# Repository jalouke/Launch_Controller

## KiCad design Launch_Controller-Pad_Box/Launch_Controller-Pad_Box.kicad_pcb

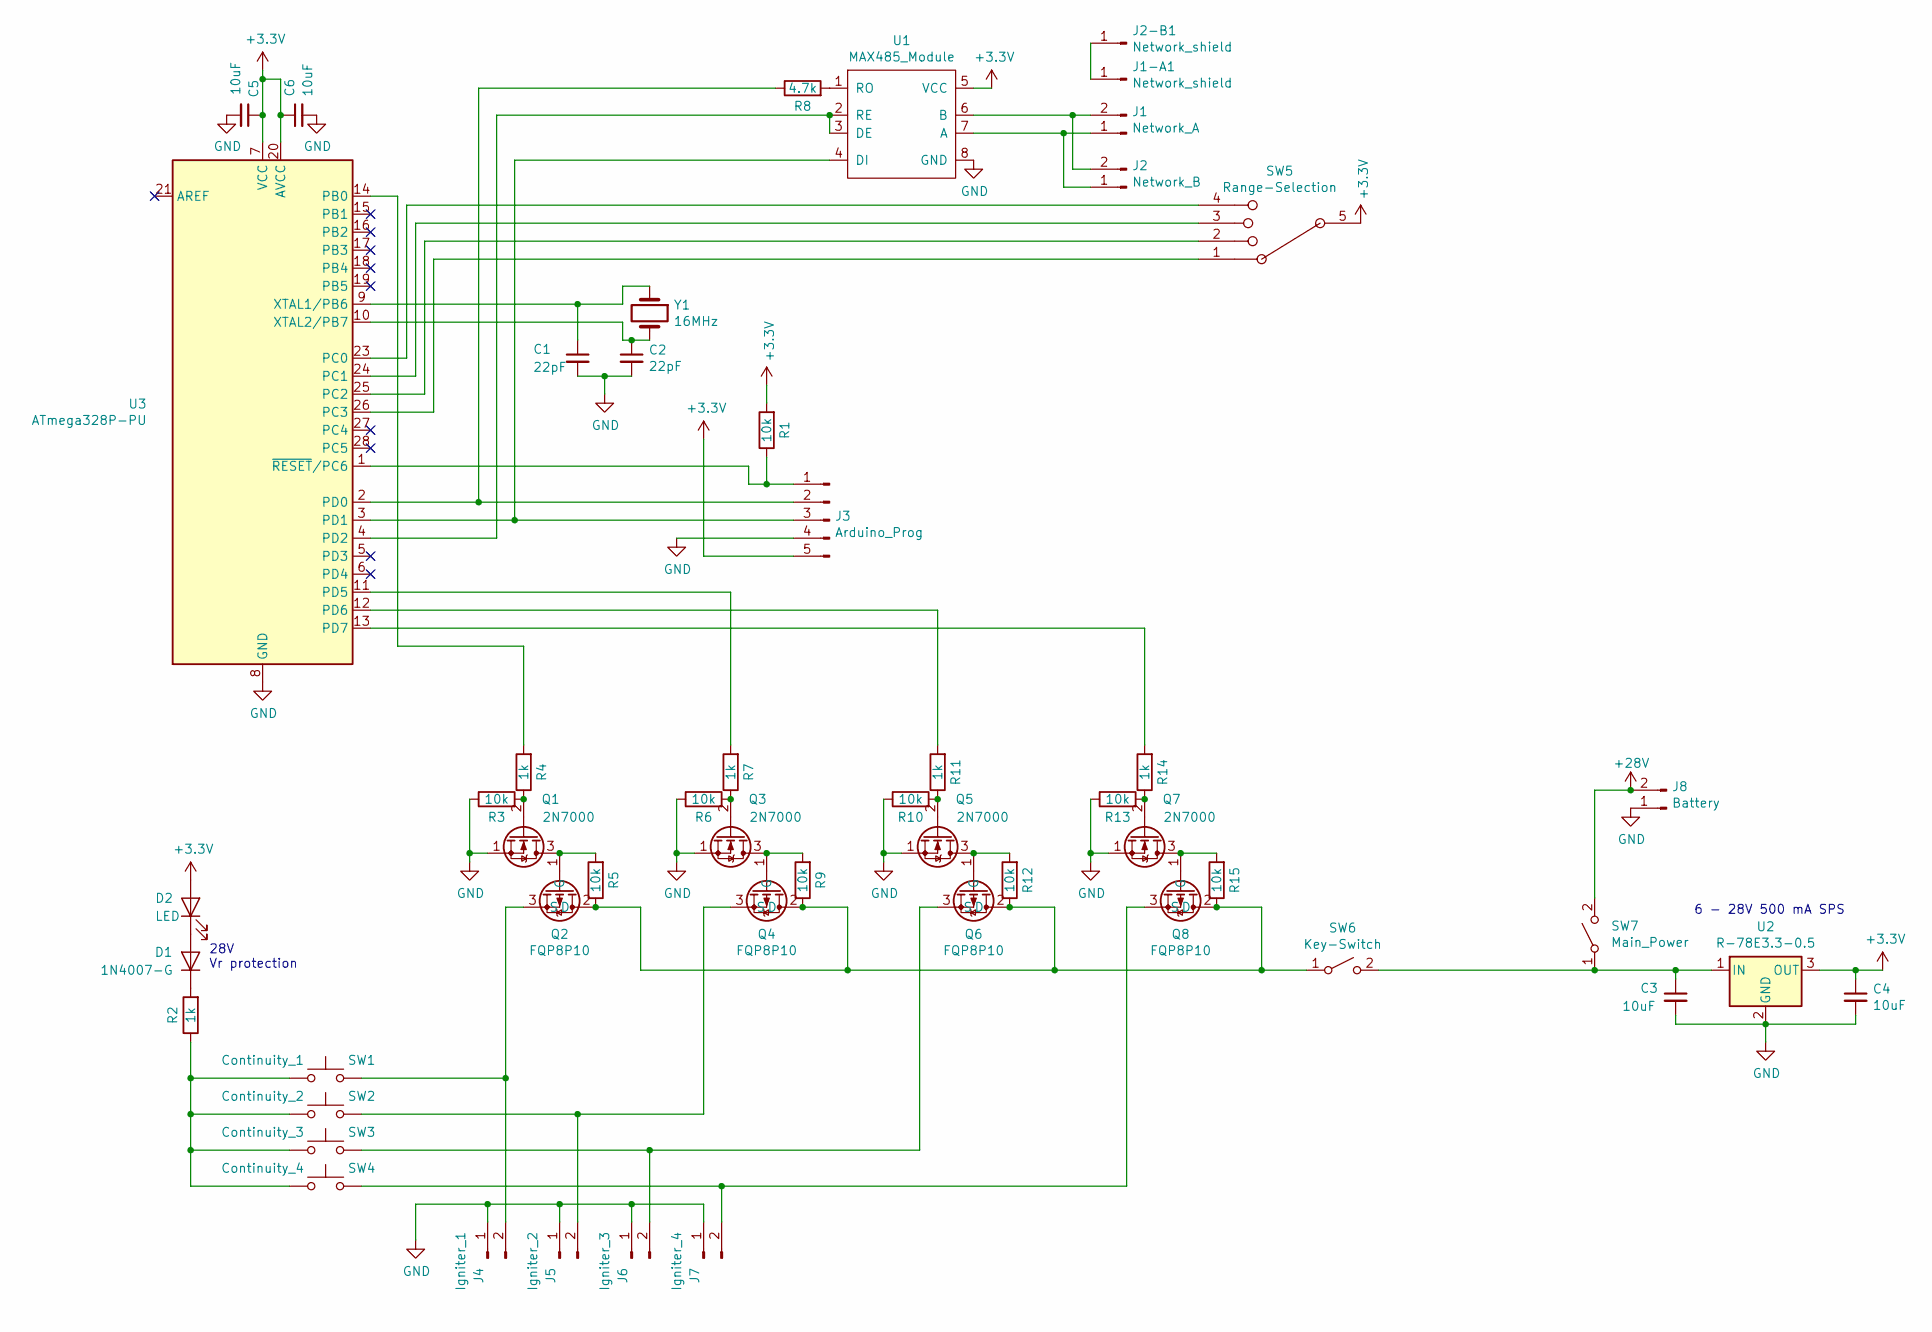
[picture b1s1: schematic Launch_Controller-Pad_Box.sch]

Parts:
C1, C2: 22pF; C_Disc_D3.0mm_W1.6mm_P2.50mm
C3, C4, C5, C6: 10uF; CP_Radial_D5.0mm_P2.00mm
D1: 1N4007-G; D_DO-41_SOD81_P10.16mm_Horizontal
D2: LED; PinHeader_2x01_P2.54mm_Vertical
J1: Network_A; PinHeader_1x02_P2.54mm_Vertical
J1-A1, J2-B1: Network_shield; PinHeader_1x01_P2.54mm_Vertical
J2: Network_B; PinHeader_1x02_P2.54mm_Vertical
J3: Arduino_Prog; PinHeader_1x05_P2.54mm_Vertical
J4: Igniter_1; PinHeader_1x02_P2.54mm_Vertical
J5: Igniter_2; PinHeader_1x02_P2.54mm_Vertical
J6: Igniter_3; PinHeader_1x02_P2.54mm_Vertical
J7: Igniter_4; PinHeader_1x02_P2.54mm_Vertical
J8: Battery; PinSocket_1x02_P2.54mm_Vertical
Q1, Q3, Q5, Q7: 2N7000; TO-92_Inline
Q2, Q4, Q6, Q8: FQP8P10; TO-220-3_Vertical
R1, R3, R5, R6, R9, R10, R12, R13, R15: 10k; R_Axial_DIN0207_L6.3mm_D2.5mm_P2.54mm_Vertical
R2, R4, R7, R11, R14: 1k; R_Axial_DIN0207_L6.3mm_D2.5mm_P2.54mm_Vertical
R8: 4.7k; R_Axial_DIN0207_L6.3mm_D2.5mm_P2.54mm_Vertical
SW1: Continuity_1; PinHeader_2x01_P2.54mm_Vertical
SW2: Continuity_2; PinHeader_2x01_P2.54mm_Vertical
SW3: Continuity_3; PinHeader_2x01_P2.54mm_Vertical
SW4: Continuity_4; PinHeader_2x01_P2.54mm_Vertical
SW5: Range-Selection; PinHeader_1x05_P2.54mm_Vertical
SW6: Key-Switch; PinHeader_1x02_P2.54mm_Vertical
SW7: Main_Power; PinHeader_1x02_P2.54mm_Vertical
U1: MAX485_Module; MAX485 Breakout
U2: R-78E3.3-0.5; Converter_DCDC_RECOM_R-78E-0.5_THT
U3: ATmega328P-PU; DIP-28_W7.62mm
Y1: 16MHz; Crystal_HC49-U_Vertical

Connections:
+3V3: C4.1, C5.1, C6.1, D2.2 (A), J3.5, R1.2, SW5.5, U1.5 (VCC), U2.3 (OUT), U3.7 (VCC), U3.20 (AVCC)
+28V: J8.2, SW7.2 (B)
GND: C1.2, C2.2, C3.2, C4.2, C5.2, C6.2, J3.4, J4.1, J5.1, J6.1, J7.1, J8.1, Q1.1 (S), Q3.1 (S), Q5.1 (S), Q7.1 (S), R3.1, R6.1, R10.1, R13.1, U1.8 (GND), U2.2 (GND), U3.8 (GND), U3.22 (GND)
unnamed: C1.1, U3.9 (XTAL1/PB6), Y1.1
unnamed: C2.1, U3.10 (XTAL2/PB7), Y1.2
unnamed: C3.1, SW6.2 (B), SW7.1 (A), U2.1 (IN)
unnamed: D1.1 (K), R2.2
unnamed: D1.2 (A), D2.1 (K)
unnamed: J1-A1.1, J2-B1.1
unnamed: J1.1, J2.1, U1.7 (A)
unnamed: J1.2, J2.2, U1.6 (B)
unnamed: J3.1, R1.1, U3.1 (~RESET~/PC6)
unnamed: J3.2, R8.1, U3.2 (PD0)
unnamed: J3.3, U1.4 (DI), U3.3 (PD1)
unnamed: J4.2, Q2.3 (S), SW1.2
unnamed: J5.2, Q4.3 (S), SW2.2
unnamed: J6.2, Q6.3 (S), SW3.2
unnamed: J7.2, Q8.3 (S), SW4.2
unnamed: Q1.2 (G), R3.2, R4.1
unnamed: Q1.3 (D), Q2.1 (G), R5.2
unnamed: Q2.2 (D), Q4.2 (D), Q6.2 (D), Q8.2 (D), R5.1, R9.1, R12.1, R15.1, SW6.1 (A)
unnamed: Q3.2 (G), R6.2, R7.1
unnamed: Q3.3 (D), Q4.1 (G), R9.2
unnamed: Q5.2 (G), R10.2, R11.1
unnamed: Q5.3 (D), Q6.1 (G), R12.2
unnamed: Q7.2 (G), R13.2, R14.1
unnamed: Q7.3 (D), Q8.1 (G), R15.2
unnamed: R2.1, SW1.1, SW2.1, SW3.1, SW4.1
unnamed: R4.2, U3.14 (PB0)
unnamed: R7.2, U3.11 (PD5)
unnamed: R8.2, U1.1 (RO)
unnamed: R11.2, U3.12 (PD6)
unnamed: R14.2, U3.13 (PD7)
unnamed: SW5.1, U3.26 (PC3)
unnamed: SW5.2, U3.25 (PC2)
unnamed: SW5.3, U3.24 (PC1)
unnamed: SW5.4, U3.23 (PC0)
unnamed: U1.2 (RE), U1.3 (DE), U3.4 (PD2)

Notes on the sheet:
6 - 28V 500 mA SPS
28V Vr protection

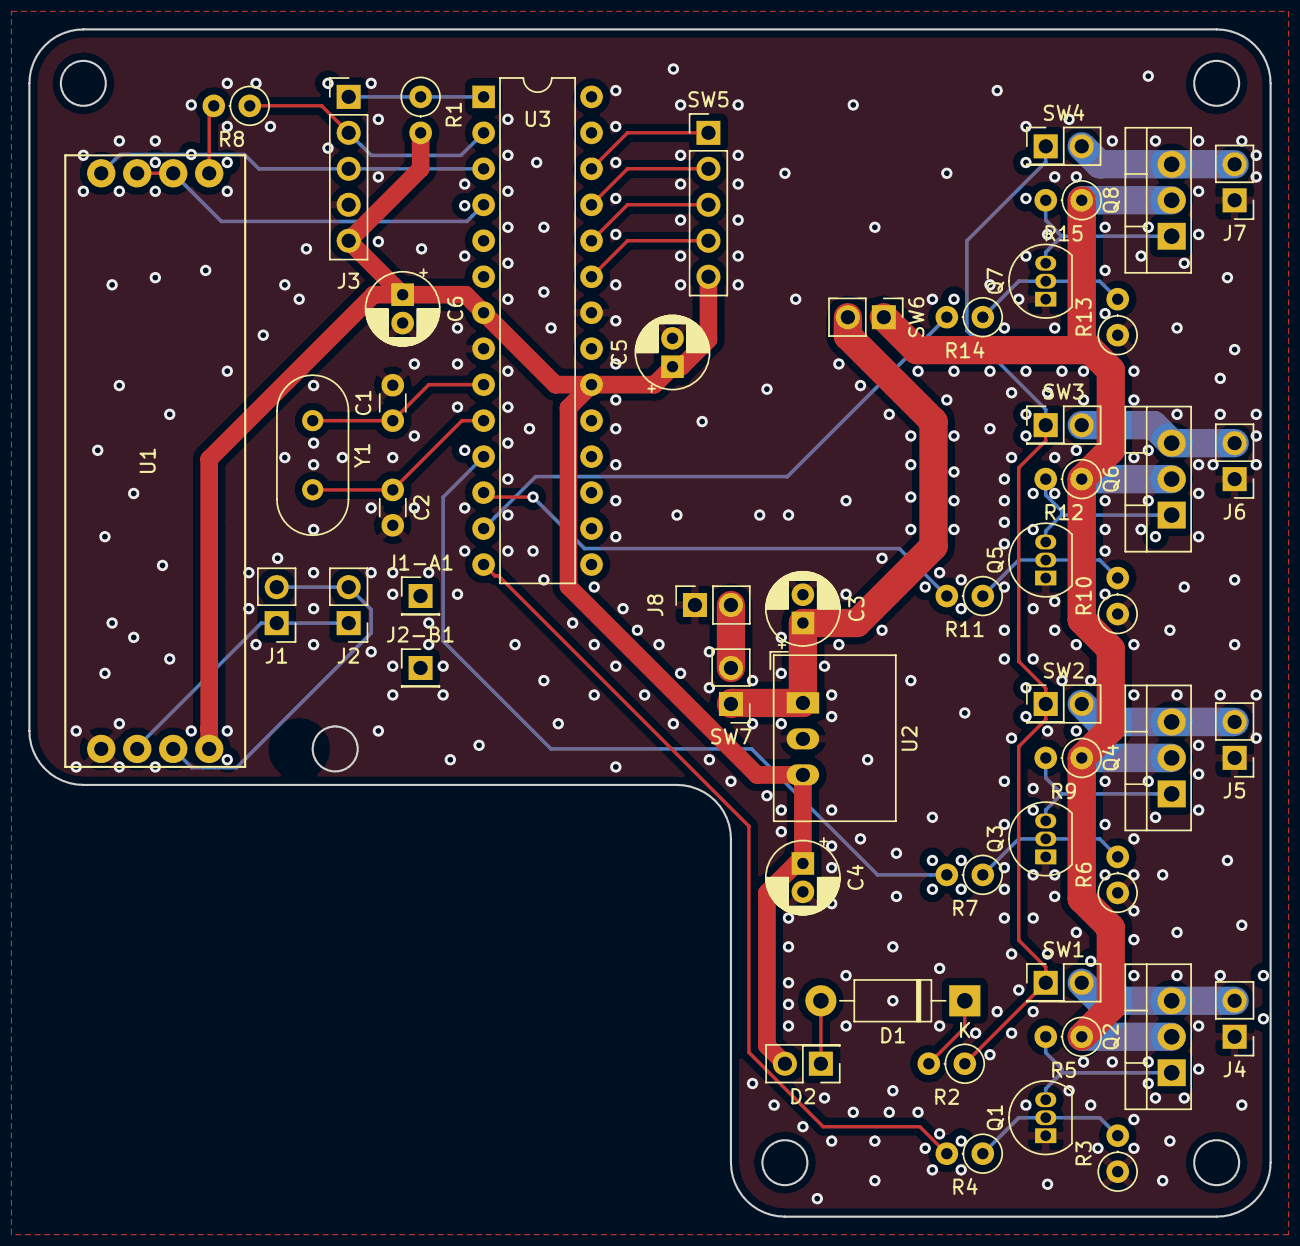
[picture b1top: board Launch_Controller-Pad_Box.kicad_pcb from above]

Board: 2 copper layers, 87.6 x 83.8 mm, 52 parts (0 on the bottom side), 38 nets.

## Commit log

2018-12-06 adding arduino code for networking arduinos. currently just testing code.
2018-12-30 working progress on circuit and layout. using MOSFETs for ignition circuit
